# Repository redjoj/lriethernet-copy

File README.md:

Project Documentation:
https://docs.google.com/document/d/17A6YyLQIsLVnjUdbRW_1tglquppojlsUYxg8EC6wMic/edit?tab=t.0

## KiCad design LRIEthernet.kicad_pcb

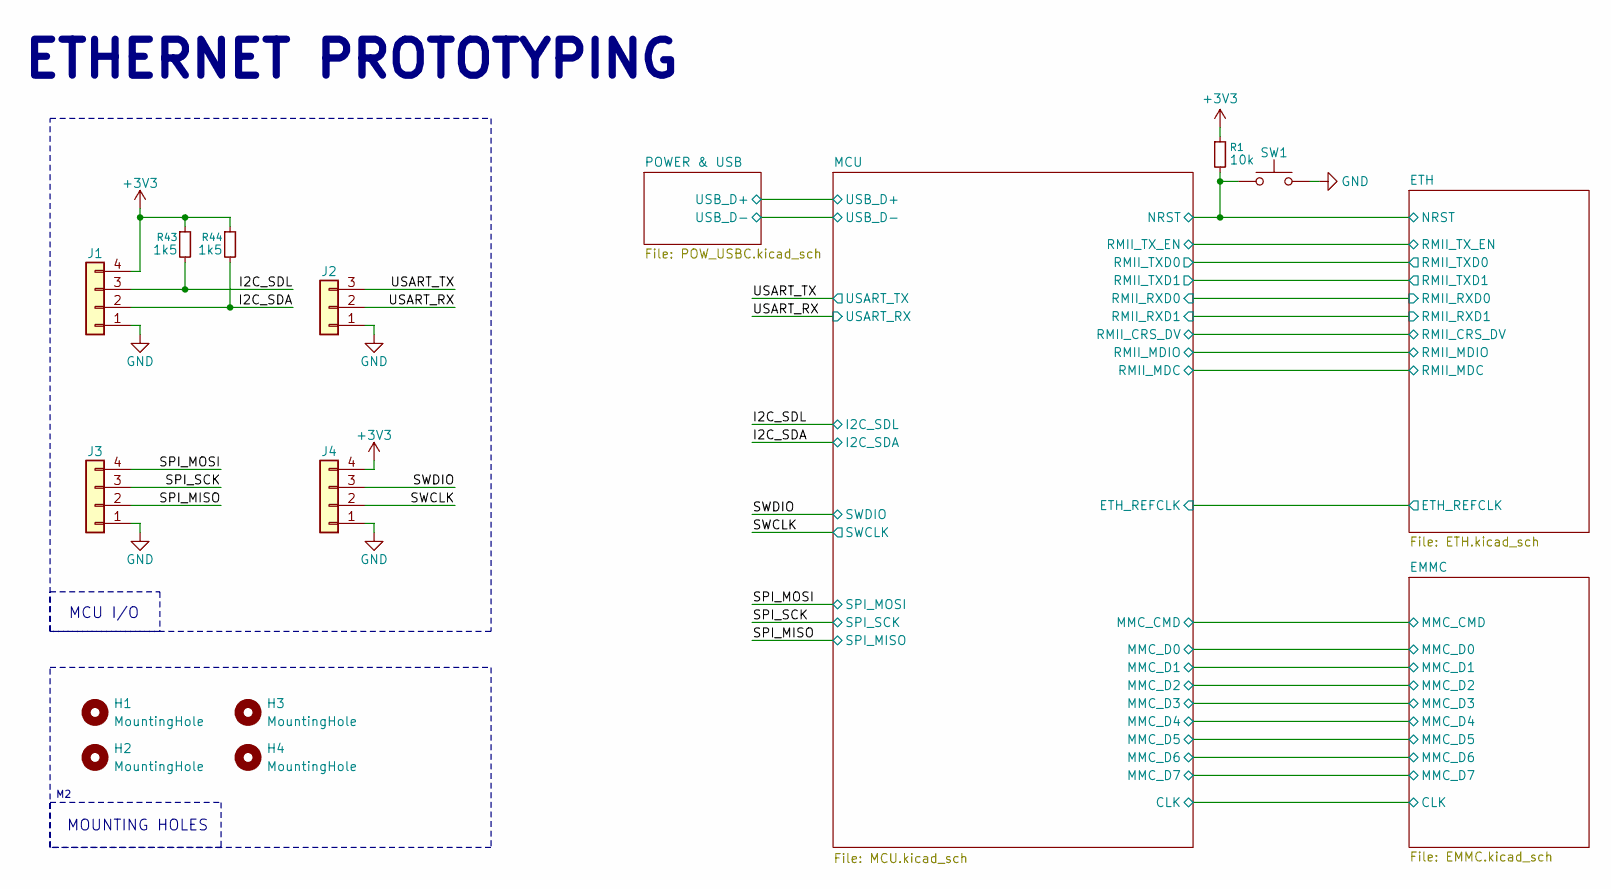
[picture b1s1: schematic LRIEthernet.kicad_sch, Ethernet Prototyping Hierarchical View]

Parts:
H1, H2, H3, H4: MountingHole; MountingHole_2.2mm_M2
J1, J3, J4: Conn_01x04; PinHeader_1x04_P2.54mm_Vertical
J2: Conn_01x03; PinHeader_1x03_P2.54mm_Vertical
R1: 10k; R_0603_1608Metric
R43, R44: 1k5; R_0603_1608Metric
SW1: SW_Push; SW_TS-1088_XNP

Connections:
+3V3: J1.4, J4.4, R1.1, R43.1, R44.1; also elsewhere on the board
/ETH/NRST: R1.2, SW1.1; also elsewhere on the board
/I2C_SDA: J1.2, R44.2; also elsewhere on the board
/I2C_SDL: J1.3, R43.2; also elsewhere on the board
/SPI_MISO: J3.2; also elsewhere on the board
/SPI_MOSI: J3.4; also elsewhere on the board
/SPI_SCK: J3.3; also elsewhere on the board
/SWCLK: J4.2; also elsewhere on the board
/SWDIO: J4.3; also elsewhere on the board
/USART_RX: J2.2; also elsewhere on the board
/USART_TX: J2.3; also elsewhere on the board
GND: J1.1, J2.1, J3.1, J4.1, SW1.2; also elsewhere on the board

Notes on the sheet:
ETHERNET PROTOTYPING
MCU I/O
MOUNTING HOLES

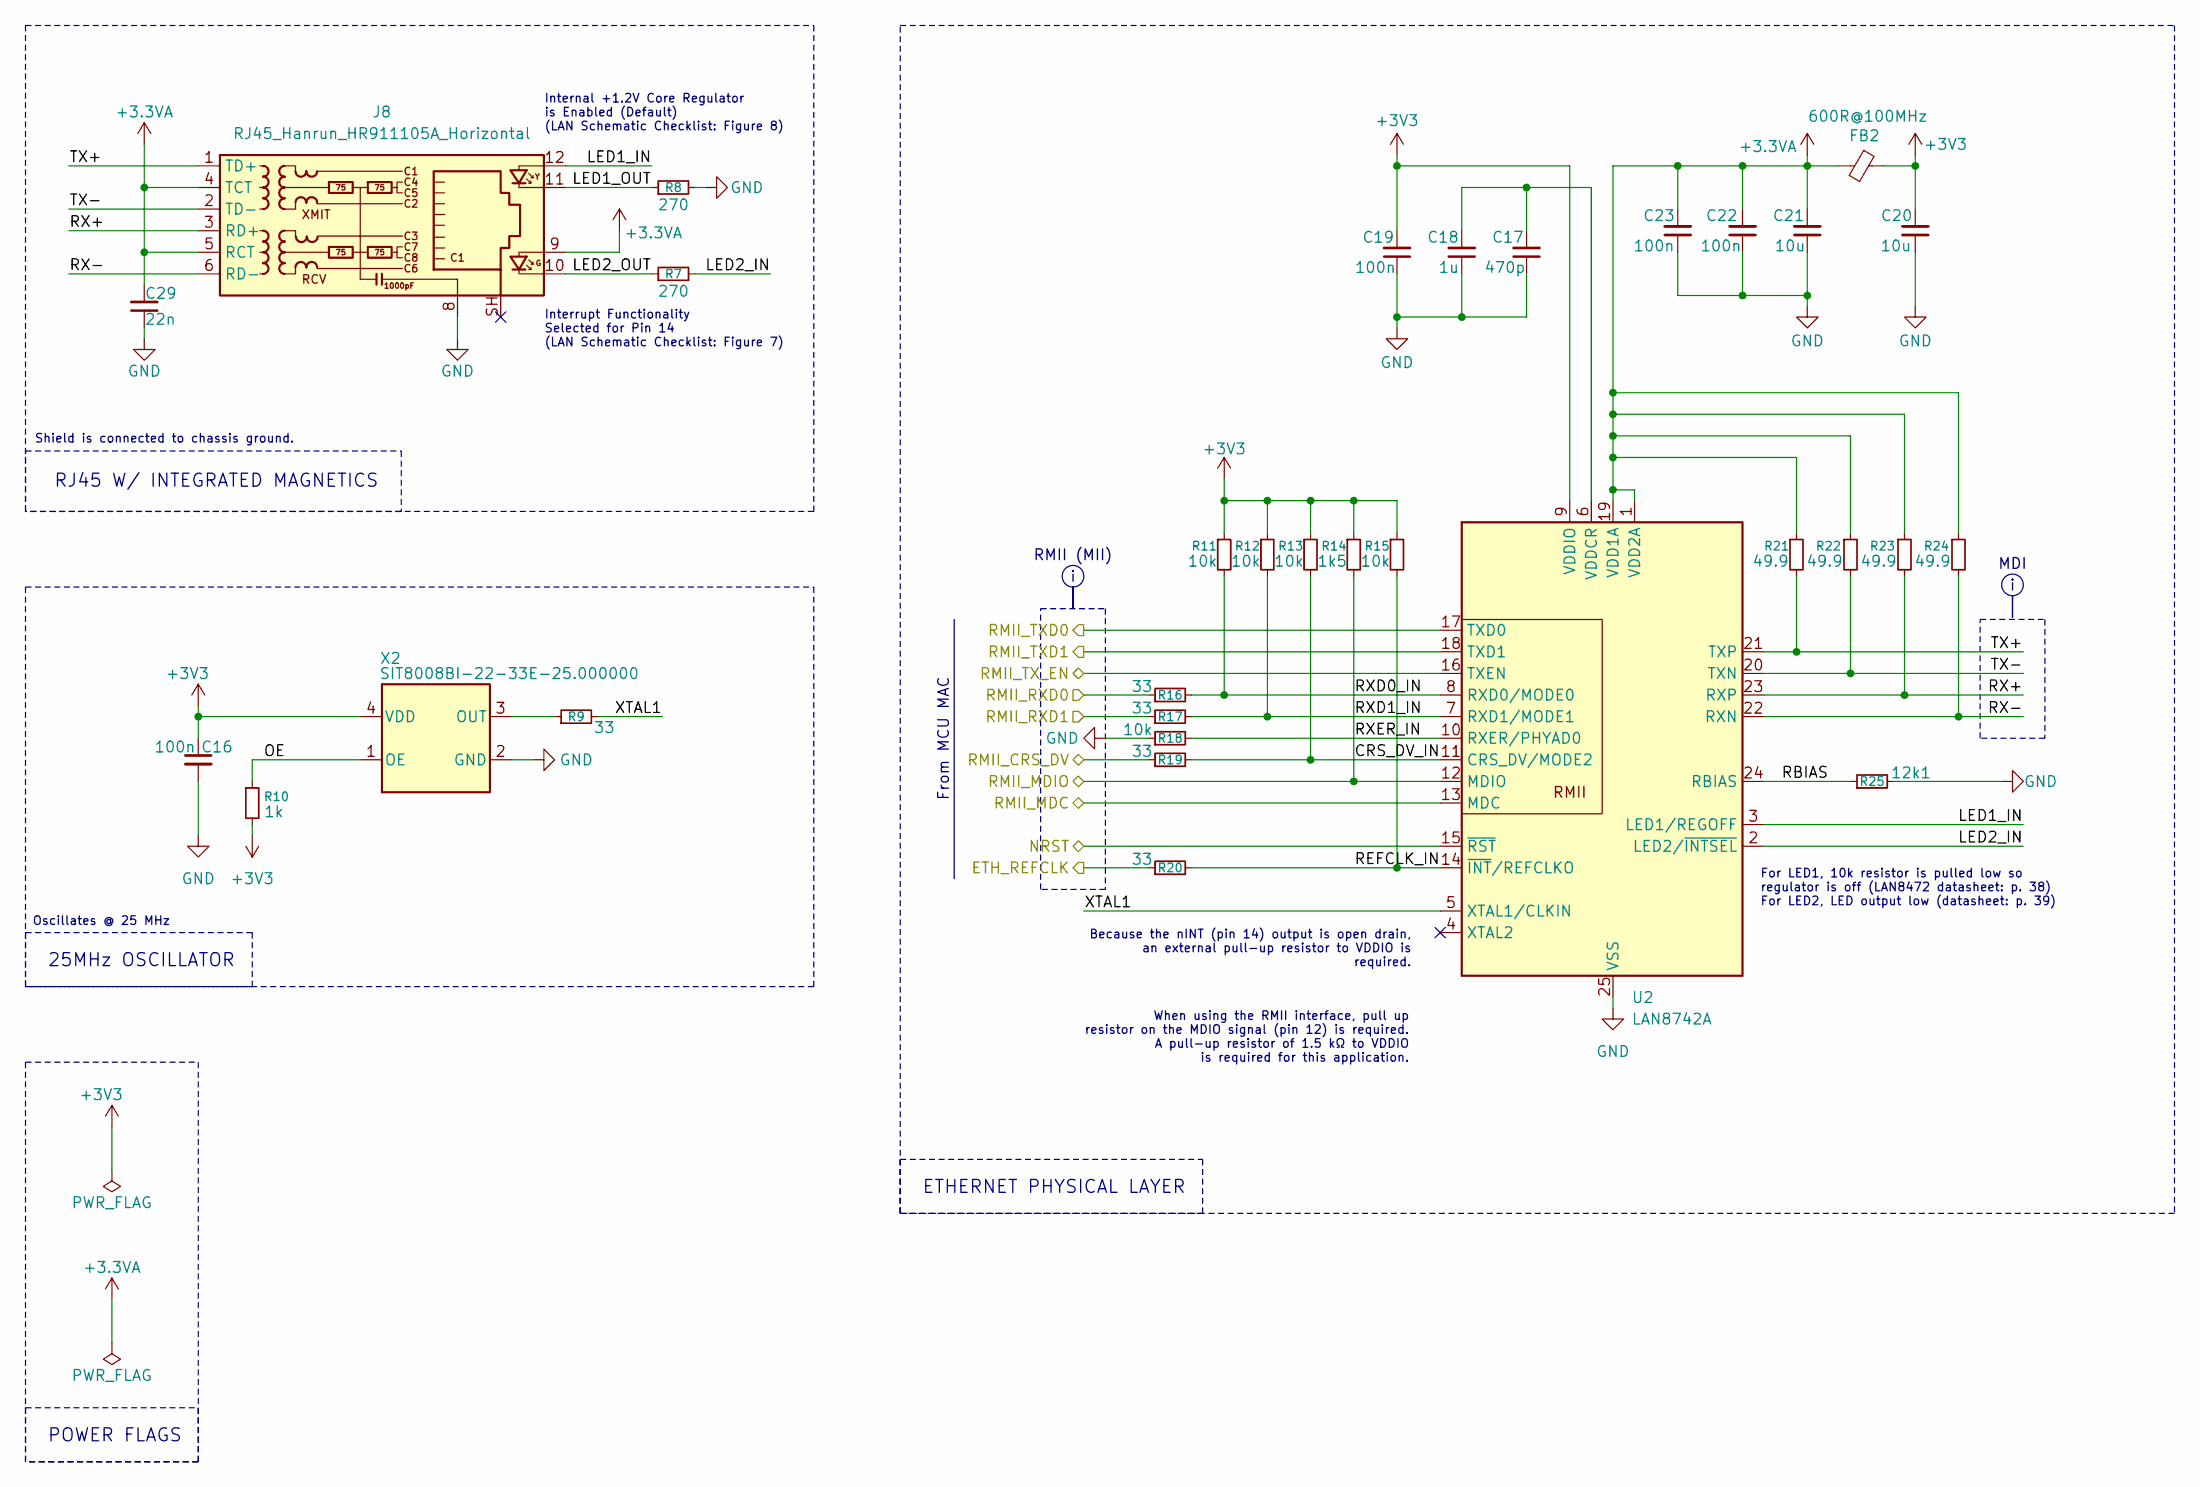
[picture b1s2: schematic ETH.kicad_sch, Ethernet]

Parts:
C16: 100n; C_0603_1608Metric
C17: 470p; C_0603_1608Metric
C18: 1u; C_0603_1608Metric
C19, C22, C23: 100n; C_0402_1005Metric
C20, C21: 10u; C_0603_1608Metric
C29: 22n; C_0603_1608Metric
FB2: 600R@100MHz; L_0603_1608Metric
J8: RJ45_Hanrun_HR911105A_Horizontal
R7, R8: 270; R_0603_1608Metric
R9, R16, R17, R19, R20: 33; R_0603_1608Metric
R10: 1k; R_0603_1608Metric
R11, R12, R13, R15, R18: 10k; R_0603_1608Metric
R14: 1k5; R_0603_1608Metric
R21, R22, R23, R24: 49.9; R_0603_1608Metric
R25: 12k1; R_0603_1608Metric
U2: LAN8742A; VQFN-24-1EP_4x4mm_P0.5mm_EP2.5x2.5mm_ThermalVias
X2: SIT8008BI-22-33E-25.000000; SON4_SIT8008BI_3.2x2.5_SIT

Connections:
+3.3VA: C21.2, C22.2, C23.2, C29.2, FB2.2, J8.4 (TCT), J8.5 (RCT), J8.9, R21.1, R22.1, R23.1, R24.1, U2.1 (VDD2A), U2.19 (VDD1A)
+3V3: C16.1, C19.2, C20.2, FB2.1, R10.2, R11.1, R12.1, R13.1, R14.1, R15.1, U2.9 (VDDIO), X2.4 (VDD); also elsewhere on the board
/ETH/ETH_REFCLK: R20.1; also elsewhere on the board
/ETH/LED1_IN: J8.12, U2.3 (LED1/REGOFF)
/ETH/LED1_OUT: J8.11, R8.1
/ETH/LED2_IN: R7.2, U2.2 (LED2/~INTSEL)
/ETH/LED2_OUT: J8.10, R7.1
/ETH/NRST: U2.15 (~RST); also elsewhere on the board
/ETH/OE: R10.1, X2.1 (OE)
/ETH/RBIAS: R25.1, U2.24 (RBIAS)
/ETH/REFCLK_IN: R15.2, R20.2, U2.14 (~INT/REFCLKO)
/ETH/RMII_CRS_DV: R19.1; also elsewhere on the board
/ETH/RMII_MDC: U2.13 (MDC); also elsewhere on the board
/ETH/RMII_RXD0: R16.1; also elsewhere on the board
/ETH/RMII_RXD1: R17.1; also elsewhere on the board
/ETH/RMII_TXD0: U2.17 (TXD0); also elsewhere on the board
/ETH/RMII_TXD1: U2.18 (TXD1); also elsewhere on the board
/ETH/RMII_TX_EN: U2.16 (TXEN); also elsewhere on the board
/ETH/RX+: J8.3 (RD+), R23.2, U2.23 (RXP)
/ETH/RX-: J8.6 (RD-), R24.2, U2.22 (RXN)
/ETH/TX+: J8.1 (TD+), R21.2, U2.21 (TXP)
/ETH/TX-: J8.2 (TD-), R22.2, U2.20 (TXN)
/ETH/XTAL1: R9.2, U2.5 (XTAL1/CLKIN)
GND: C16.2, C17.1, C18.1, C19.1, C20.1, C21.1, C22.1, C23.1, C29.1, J8.8, R8.2, R18.1, R25.2, U2.25 (VSS), X2.2 (GND); also elsewhere on the board
unnamed: C17.2, C18.2, U2.6 (VDDCR)
unnamed: R9.1, X2.3 (OUT)

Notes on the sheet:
POWER FLAGS
From MCU MAC
ETHERNET PHYSICAL LAYER
RJ45 W/ INTEGRATED MAGNETICS
Shield is connected to chassis ground.
For LED1, 10k resistor is pulled low so regulator is off (LAN8472 datasheet: p. 38) For LED2, LED output low (datasheet: p. 39)
Interrupt Functionality Selected for Pin 14 (LAN Schematic Checklist: Figure 7)
When using the RMII interface, pull up resistor on the MDIO signal (pin 12) is required. A pull-up resistor of 1.5 kΩ to VDDIO is required for this application.
RMII (MII)
25MHz OSCILLATOR
Oscillates @ 25 MHz
MDI
Internal +1.2V Core Regulator is Enabled (Default) (LAN Schematic Checklist: Figure 8)
Because the nINT (pin 14) output is open drain, an external pull-up resistor to VDDIO is required.

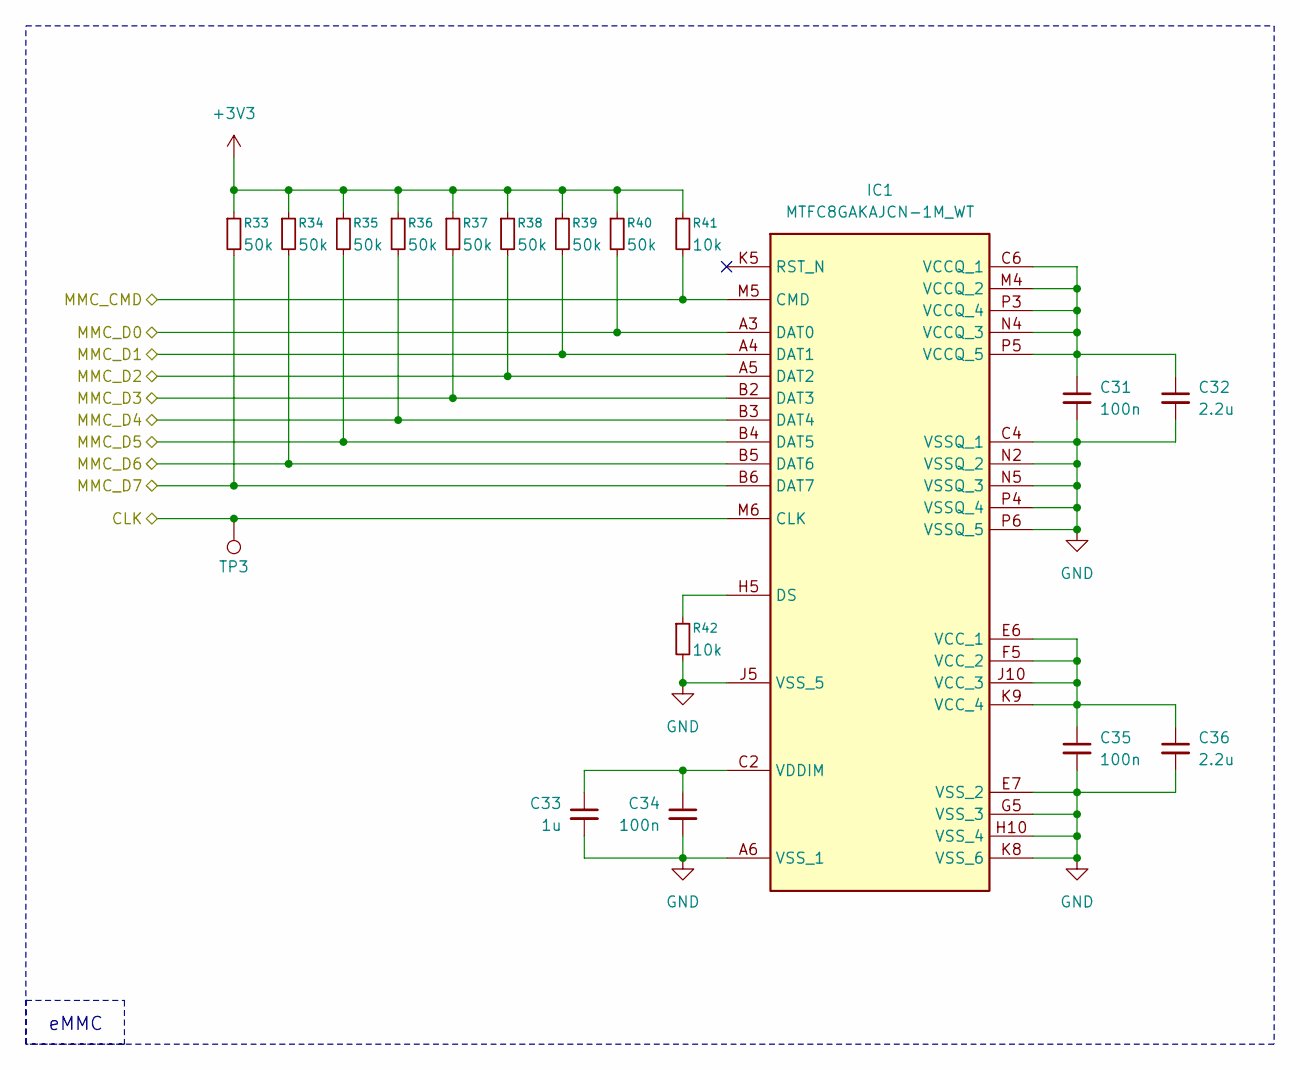
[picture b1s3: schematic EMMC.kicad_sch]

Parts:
C31, C34, C35: 100n; C_0402_1005Metric
C32, C36: 2.2u; C_0603_1608Metric
C33: 1u; C_0603_1608Metric
IC1: MTFC8GAKAJCN-1M_WT; VFBGA153_11p5X13p0X1p0_CN_MRN; Manufacturer_Part_Number MTFC8GAKAJCN-1M WT; Mouser Part Number 340-296537-TRAY
R33, R34, R35, R36, R37, R38, R39, R40: 50k; R_0603_1608Metric
R41, R42: 10k; R_0603_1608Metric
TP3: TestPoint; TestPoint_Pad_D1.0mm

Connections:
+3V3: R33.1, R34.1, R35.1, R36.1, R37.1, R38.1, R39.1, R40.1, R41.1; also elsewhere on the board
/EMMC/CLK: IC1.M6 (CLK), TP3.1; also elsewhere on the board
/EMMC/MMC_CMD: IC1.M5 (CMD), R41.2; also elsewhere on the board
/EMMC/MMC_D0: IC1.A3 (DAT0), R40.2; also elsewhere on the board
/EMMC/MMC_D1: IC1.A4 (DAT1), R39.2; also elsewhere on the board
/EMMC/MMC_D2: IC1.A5 (DAT2), R38.2; also elsewhere on the board
/EMMC/MMC_D3: IC1.B2 (DAT3), R37.2; also elsewhere on the board
/EMMC/MMC_D4: IC1.B3 (DAT4), R36.2; also elsewhere on the board
/EMMC/MMC_D5: IC1.B4 (DAT5), R35.2; also elsewhere on the board
/EMMC/MMC_D6: IC1.B5 (DAT6), R34.2; also elsewhere on the board
/EMMC/MMC_D7: IC1.B6 (DAT7), R33.2; also elsewhere on the board
GND: C31.2, C32.2, C33.2, C34.2, C35.2, C36.2, IC1.A6 (VSS_1), IC1.C4 (VSSQ_1), IC1.E7 (VSS_2), IC1.G5 (VSS_3), IC1.H10 (VSS_4), IC1.J5 (VSS_5), IC1.K8 (VSS_6), IC1.N2 (VSSQ_2), IC1.N5 (VSSQ_3), IC1.P4 (VSSQ_4), IC1.P6 (VSSQ_5), R42.2; also elsewhere on the board
unnamed: IC1.H5 (DS), R42.1
unnamed: C31.1, C32.1, IC1.C6 (VCCQ_1), IC1.M4 (VCCQ_2), IC1.N4 (VCCQ_3), IC1.P3 (VCCQ_4), IC1.P5 (VCCQ_5)
unnamed: C35.1, C36.1, IC1.E6 (VCC_1), IC1.F5 (VCC_2), IC1.J10 (VCC_3), IC1.K9 (VCC_4)
unnamed: C33.1, C34.1, IC1.C2 (VDDIM)

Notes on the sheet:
eMMC

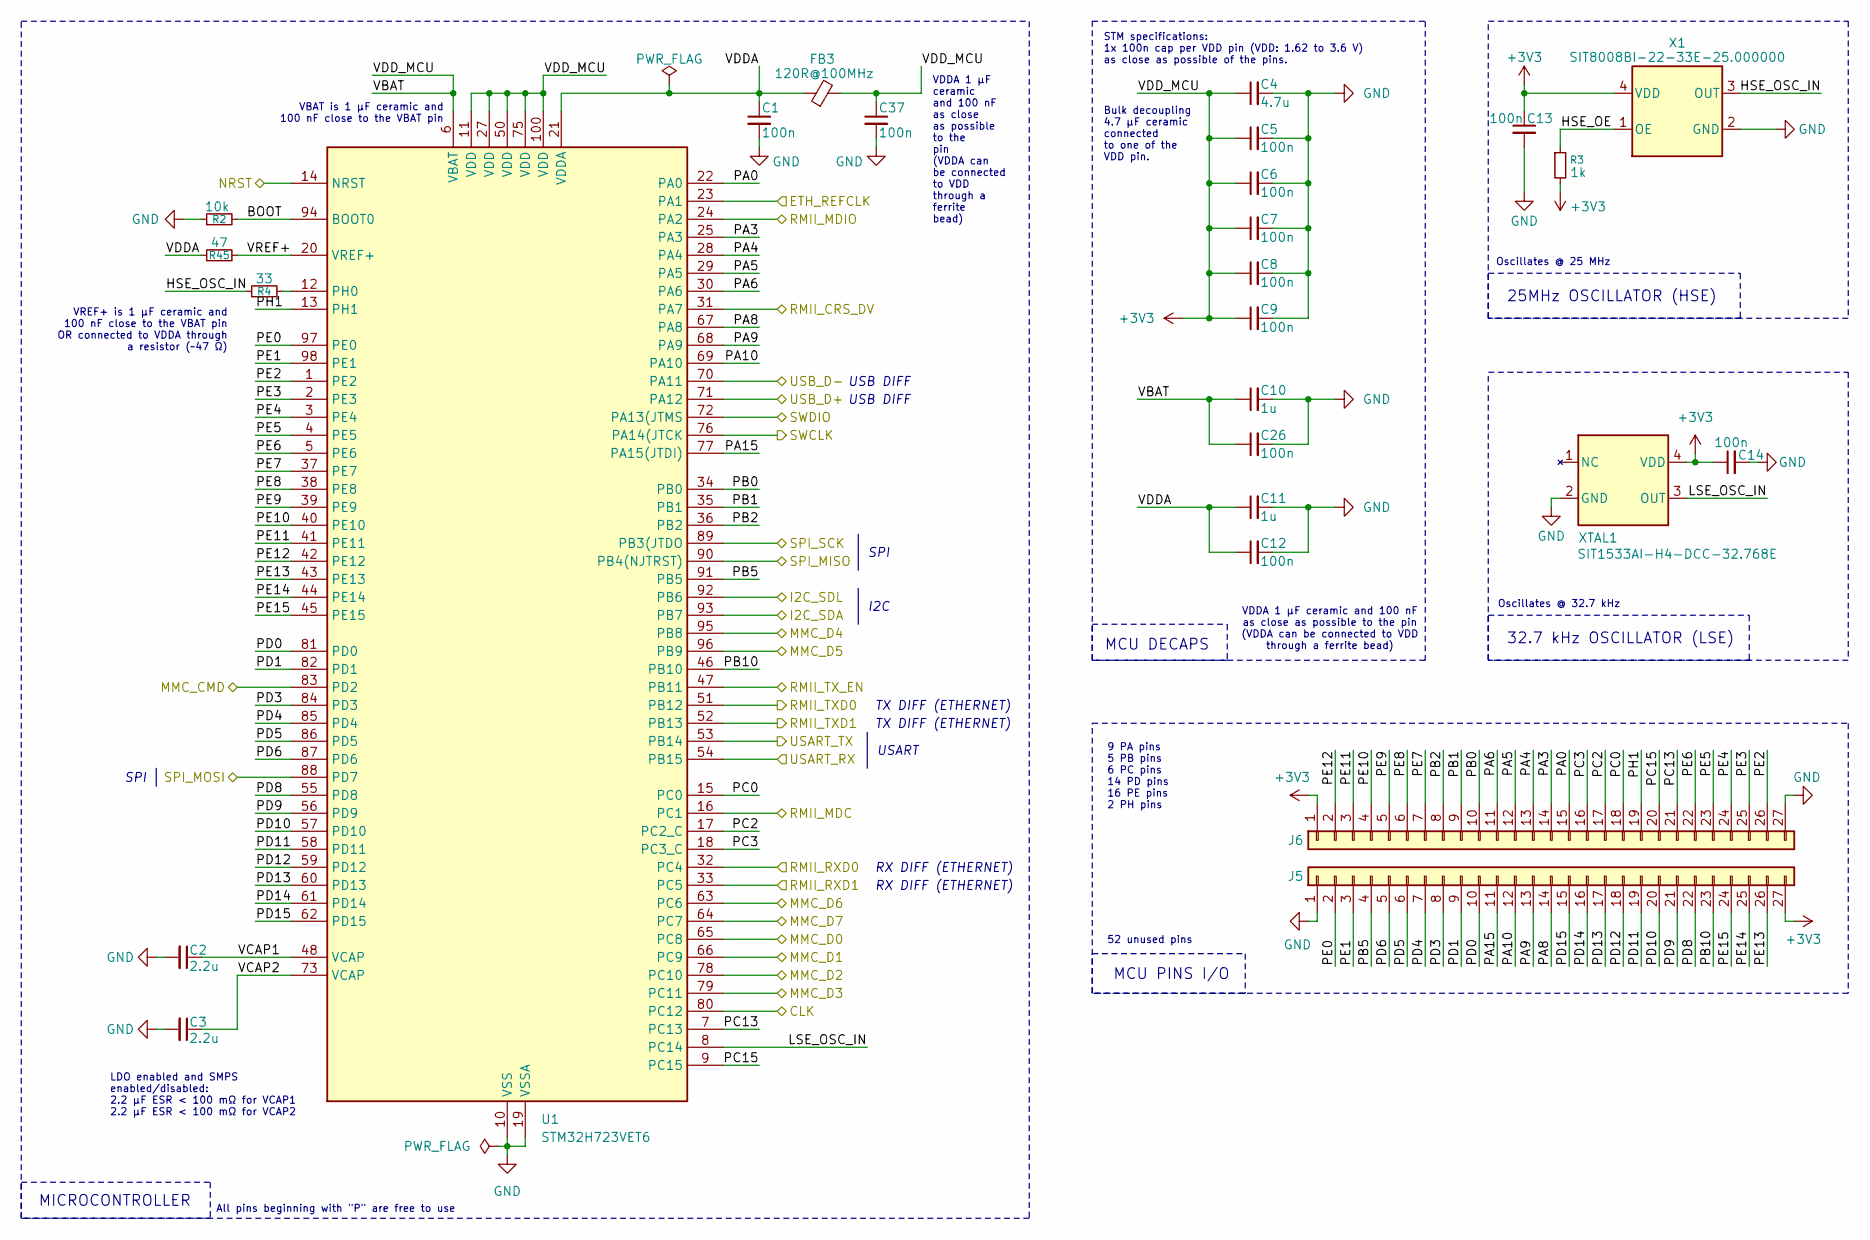
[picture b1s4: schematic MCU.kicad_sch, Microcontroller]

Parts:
C1, C5, C6, C7, C8, C9, C12, C13, C14, C26, C37: 100n; C_0402_1005Metric
C2, C3: 2.2u; C_0603_1608Metric
C4: 4.7u; C_0603_1608Metric
C10, C11: 1u; C_0603_1608Metric
FB3: 120R@100MHz; L_0603_1608Metric
J5, J6: Conn_01x27; PinHeader_1x27_P2.54mm_Vertical
R2: 10k; R_0603_1608Metric
R3: 1k; R_0603_1608Metric
R4: 33; R_0603_1608Metric
R45: 47; R_0603_1608Metric
U1: STM32H723VET6; LQFP-100_14x14mm_P0.5mm
X1: SIT8008BI-22-33E-25.000000; SON4_SIT8008BI_3.2x2.5_SIT
XTAL1: SIT1533AI-H4-DCC-32.768E; XTAL4_SiT1533_SIT

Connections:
+3V3: C4.1, C5.1, C6.1, C7.1, C8.1, C9.1, C10.1, C13.1, C14.1, C26.1, C37.1, FB3.2, J5.27, J6.1, R3.2, U1.6 (VBAT), U1.11 (VDD), U1.27 (VDD), U1.50 (VDD), U1.75 (VDD), U1.100 (VDD), X1.4 (VDD), XTAL1.4 (VDD); also elsewhere on the board
/EMMC/CLK: U1.80 (PC12); also elsewhere on the board
/EMMC/MMC_CMD: U1.83 (PD2); also elsewhere on the board
/EMMC/MMC_D0: U1.65 (PC8); also elsewhere on the board
/EMMC/MMC_D1: U1.66 (PC9); also elsewhere on the board
/EMMC/MMC_D2: U1.78 (PC10); also elsewhere on the board
/EMMC/MMC_D3: U1.79 (PC11); also elsewhere on the board
/EMMC/MMC_D4: U1.95 (PB8); also elsewhere on the board
/EMMC/MMC_D5: U1.96 (PB9); also elsewhere on the board
/EMMC/MMC_D6: U1.63 (PC6); also elsewhere on the board
/EMMC/MMC_D7: U1.64 (PC7); also elsewhere on the board
/ETH/ETH_REFCLK: U1.23 (PA1); also elsewhere on the board
/ETH/NRST: U1.14 (NRST); also elsewhere on the board
/ETH/RMII_CRS_DV: U1.31 (PA7); also elsewhere on the board
/ETH/RMII_MDC: U1.16 (PC1); also elsewhere on the board
/ETH/RMII_RXD0: U1.32 (PC4); also elsewhere on the board
/ETH/RMII_RXD1: U1.33 (PC5); also elsewhere on the board
/ETH/RMII_TXD0: U1.51 (PB12); also elsewhere on the board
/ETH/RMII_TXD1: U1.52 (PB13); also elsewhere on the board
/ETH/RMII_TX_EN: U1.47 (PB11); also elsewhere on the board
/I2C_SDA: U1.93 (PB7); also elsewhere on the board
/I2C_SDL: U1.92 (PB6); also elsewhere on the board
/MCU/BOOT: R2.2, U1.94 (BOOT0)
/MCU/HSE_OE: R3.1, X1.1 (OE)
/MCU/HSE_OSC_IN: R4.1, X1.3 (OUT)
/MCU/LSE_OSC_IN: U1.8 (PC14), XTAL1.3 (OUT)
/MCU/PA0: J6.15, U1.22 (PA0)
/MCU/PA3: J6.14, U1.25 (PA3)
/MCU/PA4: J6.13, U1.28 (PA4)
/MCU/PA5: J6.12, U1.29 (PA5)
/MCU/PA6: J6.11, U1.30 (PA6)
/MCU/PA8: J5.14, U1.67 (PA8)
/MCU/PA9: J5.13, U1.68 (PA9)
/MCU/PA10: J5.12, U1.69 (PA10)
/MCU/PA15: J5.11, U1.77 (PA15(JTDI))
/MCU/PB0: J6.10, U1.34 (PB0)
/MCU/PB1: J6.9, U1.35 (PB1)
/MCU/PB2: J6.8, U1.36 (PB2)
/MCU/PB5: J5.4, U1.91 (PB5)
/MCU/PB10: J5.23, U1.46 (PB10)
/MCU/PC0: J6.18, U1.15 (PC0)
/MCU/PC2: J6.17, U1.17 (PC2_C)
/MCU/PC3: J6.16, U1.18 (PC3_C)
/MCU/PC13: J6.21, U1.7 (PC13)
/MCU/PC15: J6.20, U1.9 (PC15)
/MCU/PD0: J5.10, U1.81 (PD0)
/MCU/PD1: J5.9, U1.82 (PD1)
/MCU/PD3: J5.8, U1.84 (PD3)
/MCU/PD4: J5.7, U1.85 (PD4)
/MCU/PD5: J5.6, U1.86 (PD5)
/MCU/PD6: J5.5, U1.87 (PD6)
/MCU/PD8: J5.22, U1.55 (PD8)
/MCU/PD9: J5.21, U1.56 (PD9)
/MCU/PD10: J5.20, U1.57 (PD10)
/MCU/PD11: J5.19, U1.58 (PD11)
/MCU/PD12: J5.18, U1.59 (PD12)
/MCU/PD13: J5.17, U1.60 (PD13)
/MCU/PD14: J5.16, U1.61 (PD14)
/MCU/PD15: J5.15, U1.62 (PD15)
/MCU/PE0: J5.2, U1.97 (PE0)
/MCU/PE1: J5.3, U1.98 (PE1)
/MCU/PE2: J6.26, U1.1 (PE2)
/MCU/PE3: J6.25, U1.2 (PE3)
/MCU/PE4: J6.24, U1.3 (PE4)
/MCU/PE5: J6.23, U1.4 (PE5)
/MCU/PE6: J6.22, U1.5 (PE6)
/MCU/PE7: J6.7, U1.37 (PE7)
/MCU/PE8: J6.6, U1.38 (PE8)
/MCU/PE9: J6.5, U1.39 (PE9)
/MCU/PE10: J6.4, U1.40 (PE10)
/MCU/PE11: J6.3, U1.41 (PE11)
/MCU/PE12: J6.2, U1.42 (PE12)
/MCU/PE13: J5.26, U1.43 (PE13)
/MCU/PE14: J5.25, U1.44 (PE14)
/MCU/PE15: J5.24, U1.45 (PE15)
/MCU/PH1: J6.19, U1.13 (PH1)
/MCU/USB_D+: U1.71 (PA12); also elsewhere on the board
/MCU/USB_D-: U1.70 (PA11); also elsewhere on the board
/MCU/VCAP1: C2.1, U1.48 (VCAP)
/MCU/VCAP2: C3.1, U1.73 (VCAP)
/MCU/VDDA: C1.1, C11.1, C12.1, FB3.1, R45.1, U1.21 (VDDA)
/MCU/VREF+: R45.2, U1.20 (VREF+)
/SPI_MISO: U1.90 (PB4(NJTRST)); also elsewhere on the board
/SPI_MOSI: U1.88 (PD7); also elsewhere on the board
/SPI_SCK: U1.89 (PB3(JTDO); also elsewhere on the board
/SWCLK: U1.76 (PA14(JTCK); also elsewhere on the board
/SWDIO: U1.72 (PA13(JTMS); also elsewhere on the board
/USART_RX: U1.54 (PB15); also elsewhere on the board
/USART_TX: U1.53 (PB14); also elsewhere on the board
GND: C1.2, C2.2, C3.2, C4.2, C5.2, C6.2, C7.2, C8.2, C9.2, C10.2, C11.2, C12.2, C13.2, C14.2, C26.2, C37.2, J5.1, J6.27, R2.1, U1.10 (VSS), U1.19 (VSSA), U1.26 (VSS), U1.49 (VSS), U1.74 (VSS), U1.99 (VSS), X1.2 (GND), XTAL1.2 (GND); also elsewhere on the board
unnamed: R4.2, U1.12 (PH0)

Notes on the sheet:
STM specifications: 1x 100n cap per VDD pin (VDD: 1.62 to 3.6 V) as close as possible of the pins.
Oscillates @ 25 MHz
VREF+ is 1 μF ceramic and 100 nF close to the VBAT pin OR connected to VDDA through a resistor (~47 Ω)
Oscillates @ 32.7 kHz
VDDA 1 μF ceramic and 100 nF as close as possible to the pin (VDDA can be connected to VDD through a ferrite bead)
RX DIFF (ETHERNET)
USART
USB DIFF
All pins beginning with "P" are free to use
VDDA 1 μF ceramic and 100 nF as close as possible to the pin (VDDA can be connected to VDD through a ferrite bead)
MICROCONTROLLER
TX DIFF (ETHERNET)
LDO enabled and SMPS enabled/disabled: 2.2 μF ESR < 100 mΩ for VCAP1 2.2 μF ESR < 100 mΩ for VCAP2
I2C
TX DIFF (ETHERNET)
SPI
MCU PINS I/O
52 unused pins
32.7 kHz OSCILLATOR (LSE)
9 PA pins 5 PB pins 6 PC pins 14 PD pins 16 PE pins 2 PH pins
Bulk decoupling 4.7 μF ceramic connected to one of the VDD pin.
MCU DECAPS
VBAT is 1 μF ceramic and 100 nF close to the VBAT pin
25MHz OSCILLATOR (HSE)

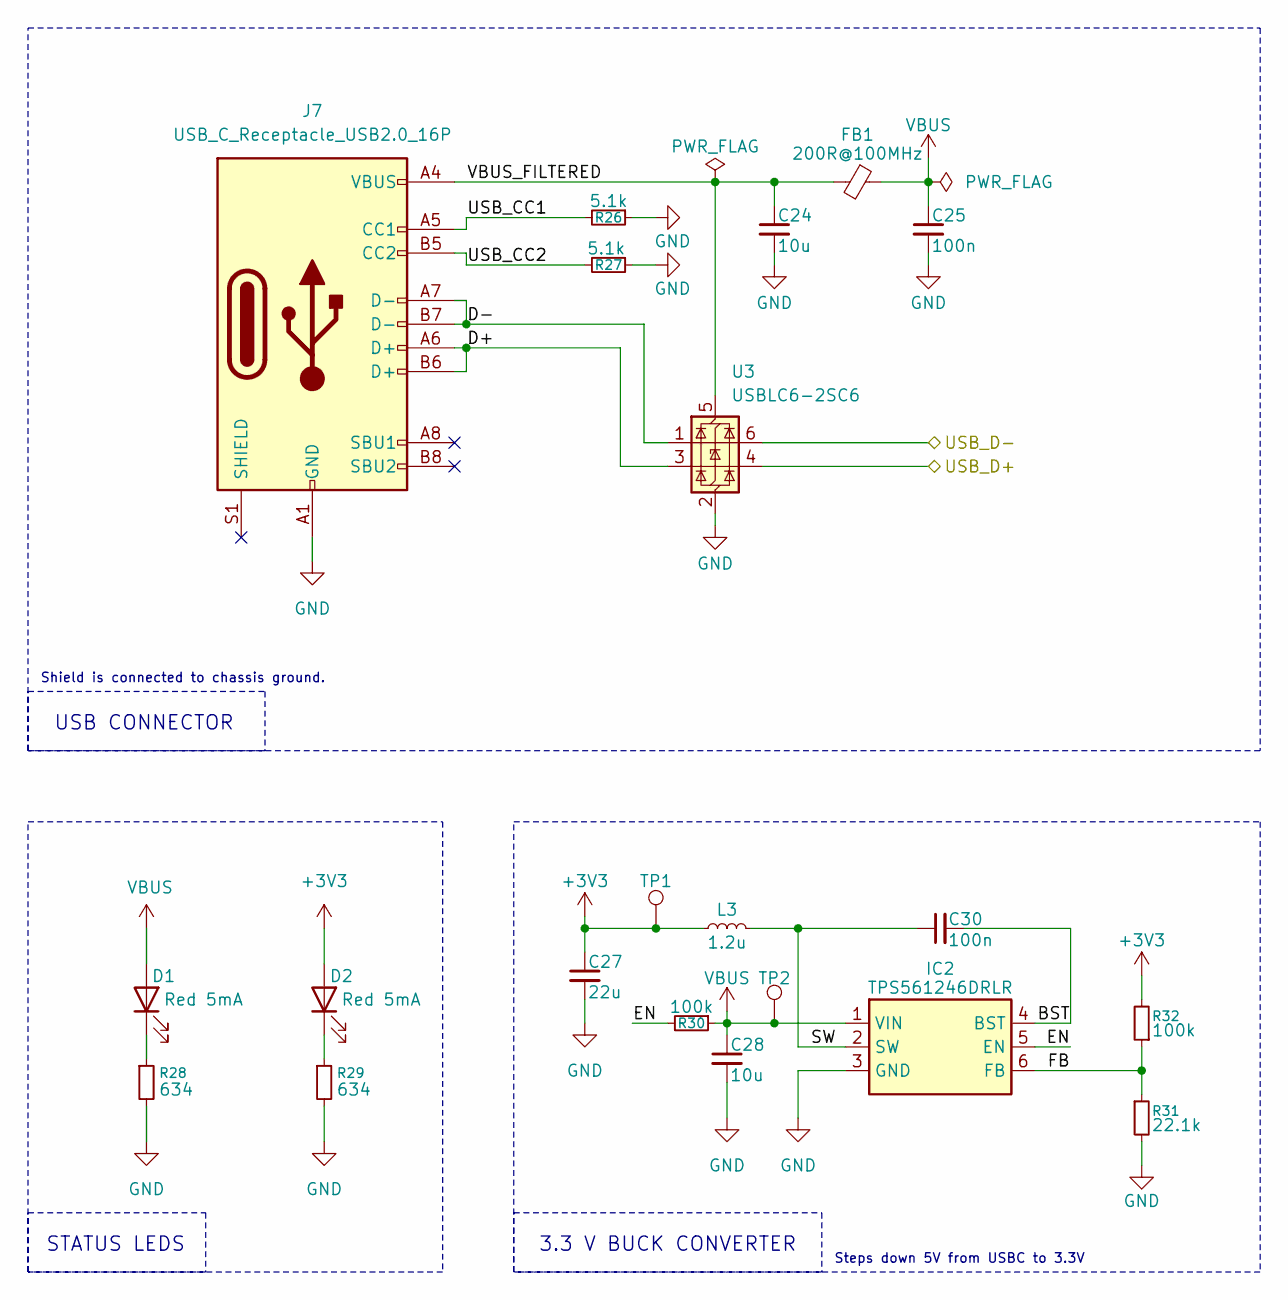
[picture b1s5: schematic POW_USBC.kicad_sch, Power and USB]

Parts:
C24: 10u; C_0603_1608Metric
C25, C30: 100n; C_0603_1608Metric
C27: 22u; C_0805_2012Metric
C28: 10u; C_0805_2012Metric
D1, D2: Red 5mA; LED_0603_1608Metric
FB1: 200R@100MHz; L_0603_1608Metric
IC2: TPS561246DRLR; SOT-563; Mouser Part Number 595-TPS561246DRLR
J7: USB_C_Receptacle_USB2.0_16P; USB_C_Receptacle_GCT_USB4110
L3: 1.2u; L_0603_1608Metric
R26, R27: 5.1k; R_0603_1608Metric
R28, R29: 634; R_0603_1608Metric
R30, R32: 100k; R_0603_1608Metric
R31: 22.1k; R_0603_1608Metric
TP1, TP2: TestPoint; TestPoint_Pad_D1.0mm
U3: USBLC6-2SC6; SOT-23-6

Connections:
+3V3: C27.1, D2.2 (A), L3.1, R32.2, TP1.1; also elsewhere on the board
/MCU/USB_D+: U3.4 (I/O2); also elsewhere on the board
/MCU/USB_D-: U3.6 (I/O1); also elsewhere on the board
/POWER & USB/BST: C30.2, IC2.4 (BST)
/POWER & USB/D+: J7.A6 (D+), J7.B6 (D+), U3.3 (I/O2)
/POWER & USB/D-: J7.A7 (D-), J7.B7 (D-), U3.1 (I/O1)
/POWER & USB/EN: IC2.5 (EN), R30.2
/POWER & USB/FB: IC2.6 (FB), R31.1, R32.1
/POWER & USB/SW: C30.1, IC2.2 (SW), L3.2
/POWER & USB/USB_CC1: J7.A5 (CC1), R26.2
/POWER & USB/USB_CC2: J7.B5 (CC2), R27.2
/POWER & USB/VBUS_FILTERED: C24.1, FB1.2, J7.A4 (VBUS), J7.A9 (VBUS), J7.B4 (VBUS), J7.B9 (VBUS), U3.5 (VBUS)
GND: C24.2, C25.2, C27.2, C28.2, IC2.3 (GND), J7.A1 (GND), J7.A12 (GND), J7.B1 (GND), J7.B12 (GND), R26.1, R27.1, R28.2, R29.2, R31.2, U3.2 (GND); also elsewhere on the board
unnamed: D1.1 (K), R28.1
unnamed: D2.1 (K), R29.1
VBUS: C25.1, C28.1, D1.2 (A), FB1.1, IC2.1 (VIN), R30.1, TP2.1

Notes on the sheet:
Shield is connected to chassis ground.
USB CONNECTOR
STATUS LEDS
3.3 V BUCK CONVERTER
Steps down 5V from USBC to 3.3V

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
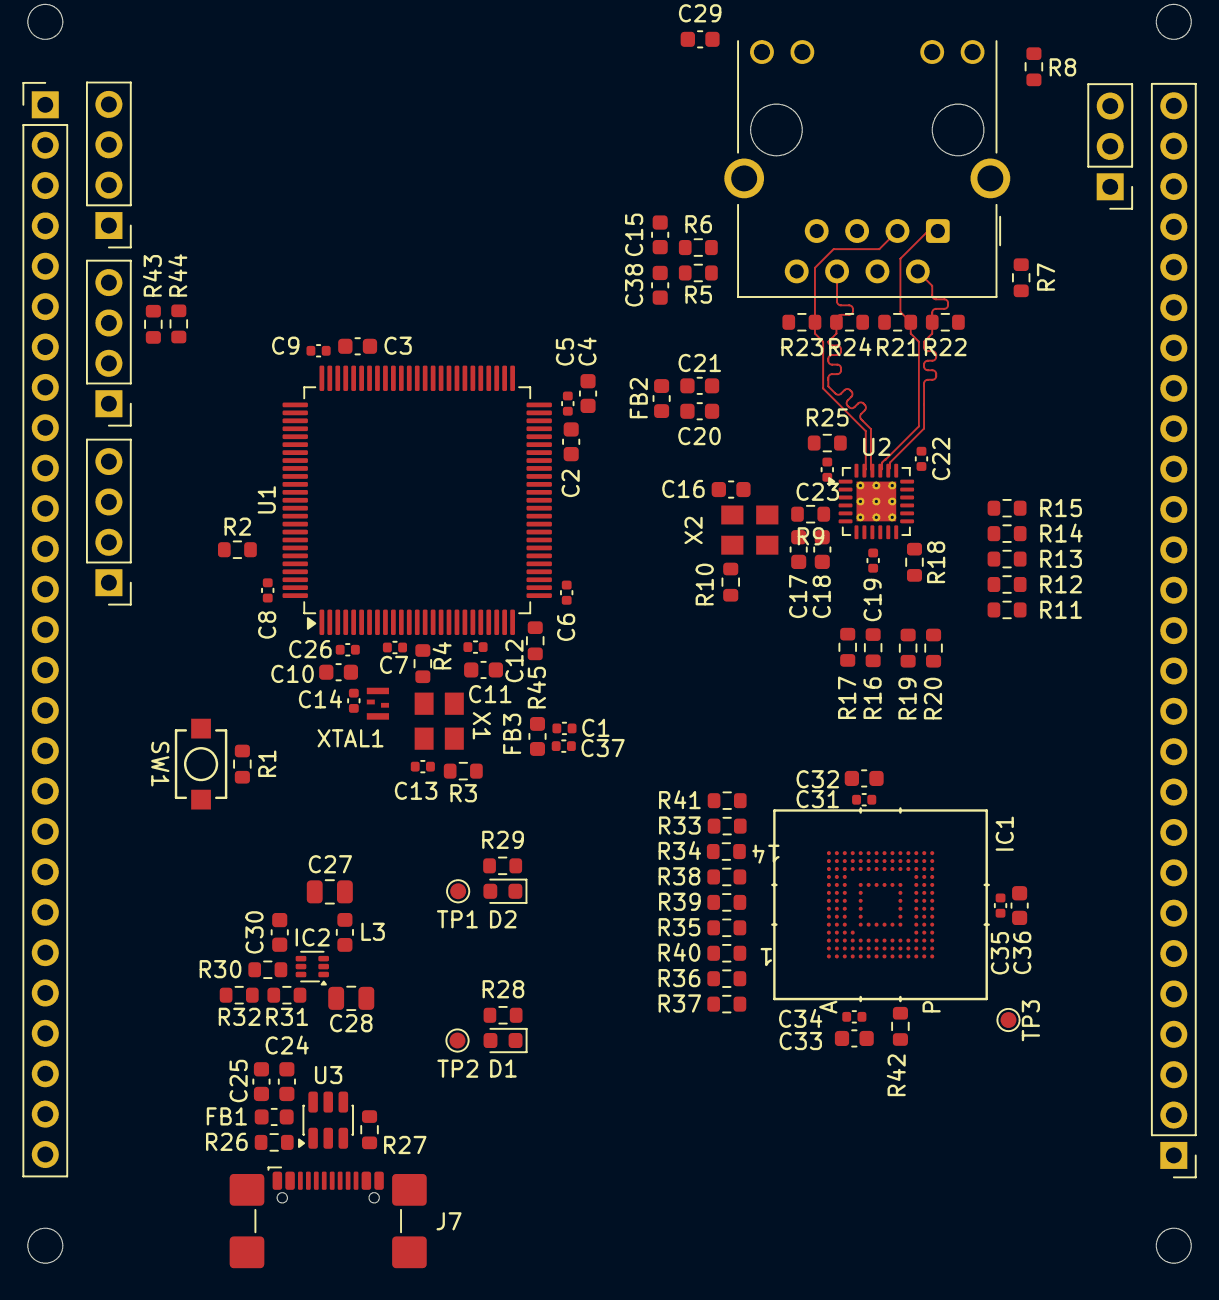
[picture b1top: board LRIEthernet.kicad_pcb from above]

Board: 4 copper layers, 113 parts (0 on the bottom side), 129 nets.

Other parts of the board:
C15, C38: 1n; C_0603_1608Metric
R5, R6: 75; R_0603_1608Metric

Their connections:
GND: C15.2, C38.2; also elsewhere on the board
unnamed: C15.1, R6.1
unnamed: C38.1, R5.1

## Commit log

2026-02-13 Copied project from LRI Github repository.
2026-02-13 Update project documentation link in README
2026-02-13 Fix link formatting in README.md
